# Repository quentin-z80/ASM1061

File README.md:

# ASM1061

ASM1061 based PCIe to SATA card

Manufactured using JLCPCB's JLC3313 stackup

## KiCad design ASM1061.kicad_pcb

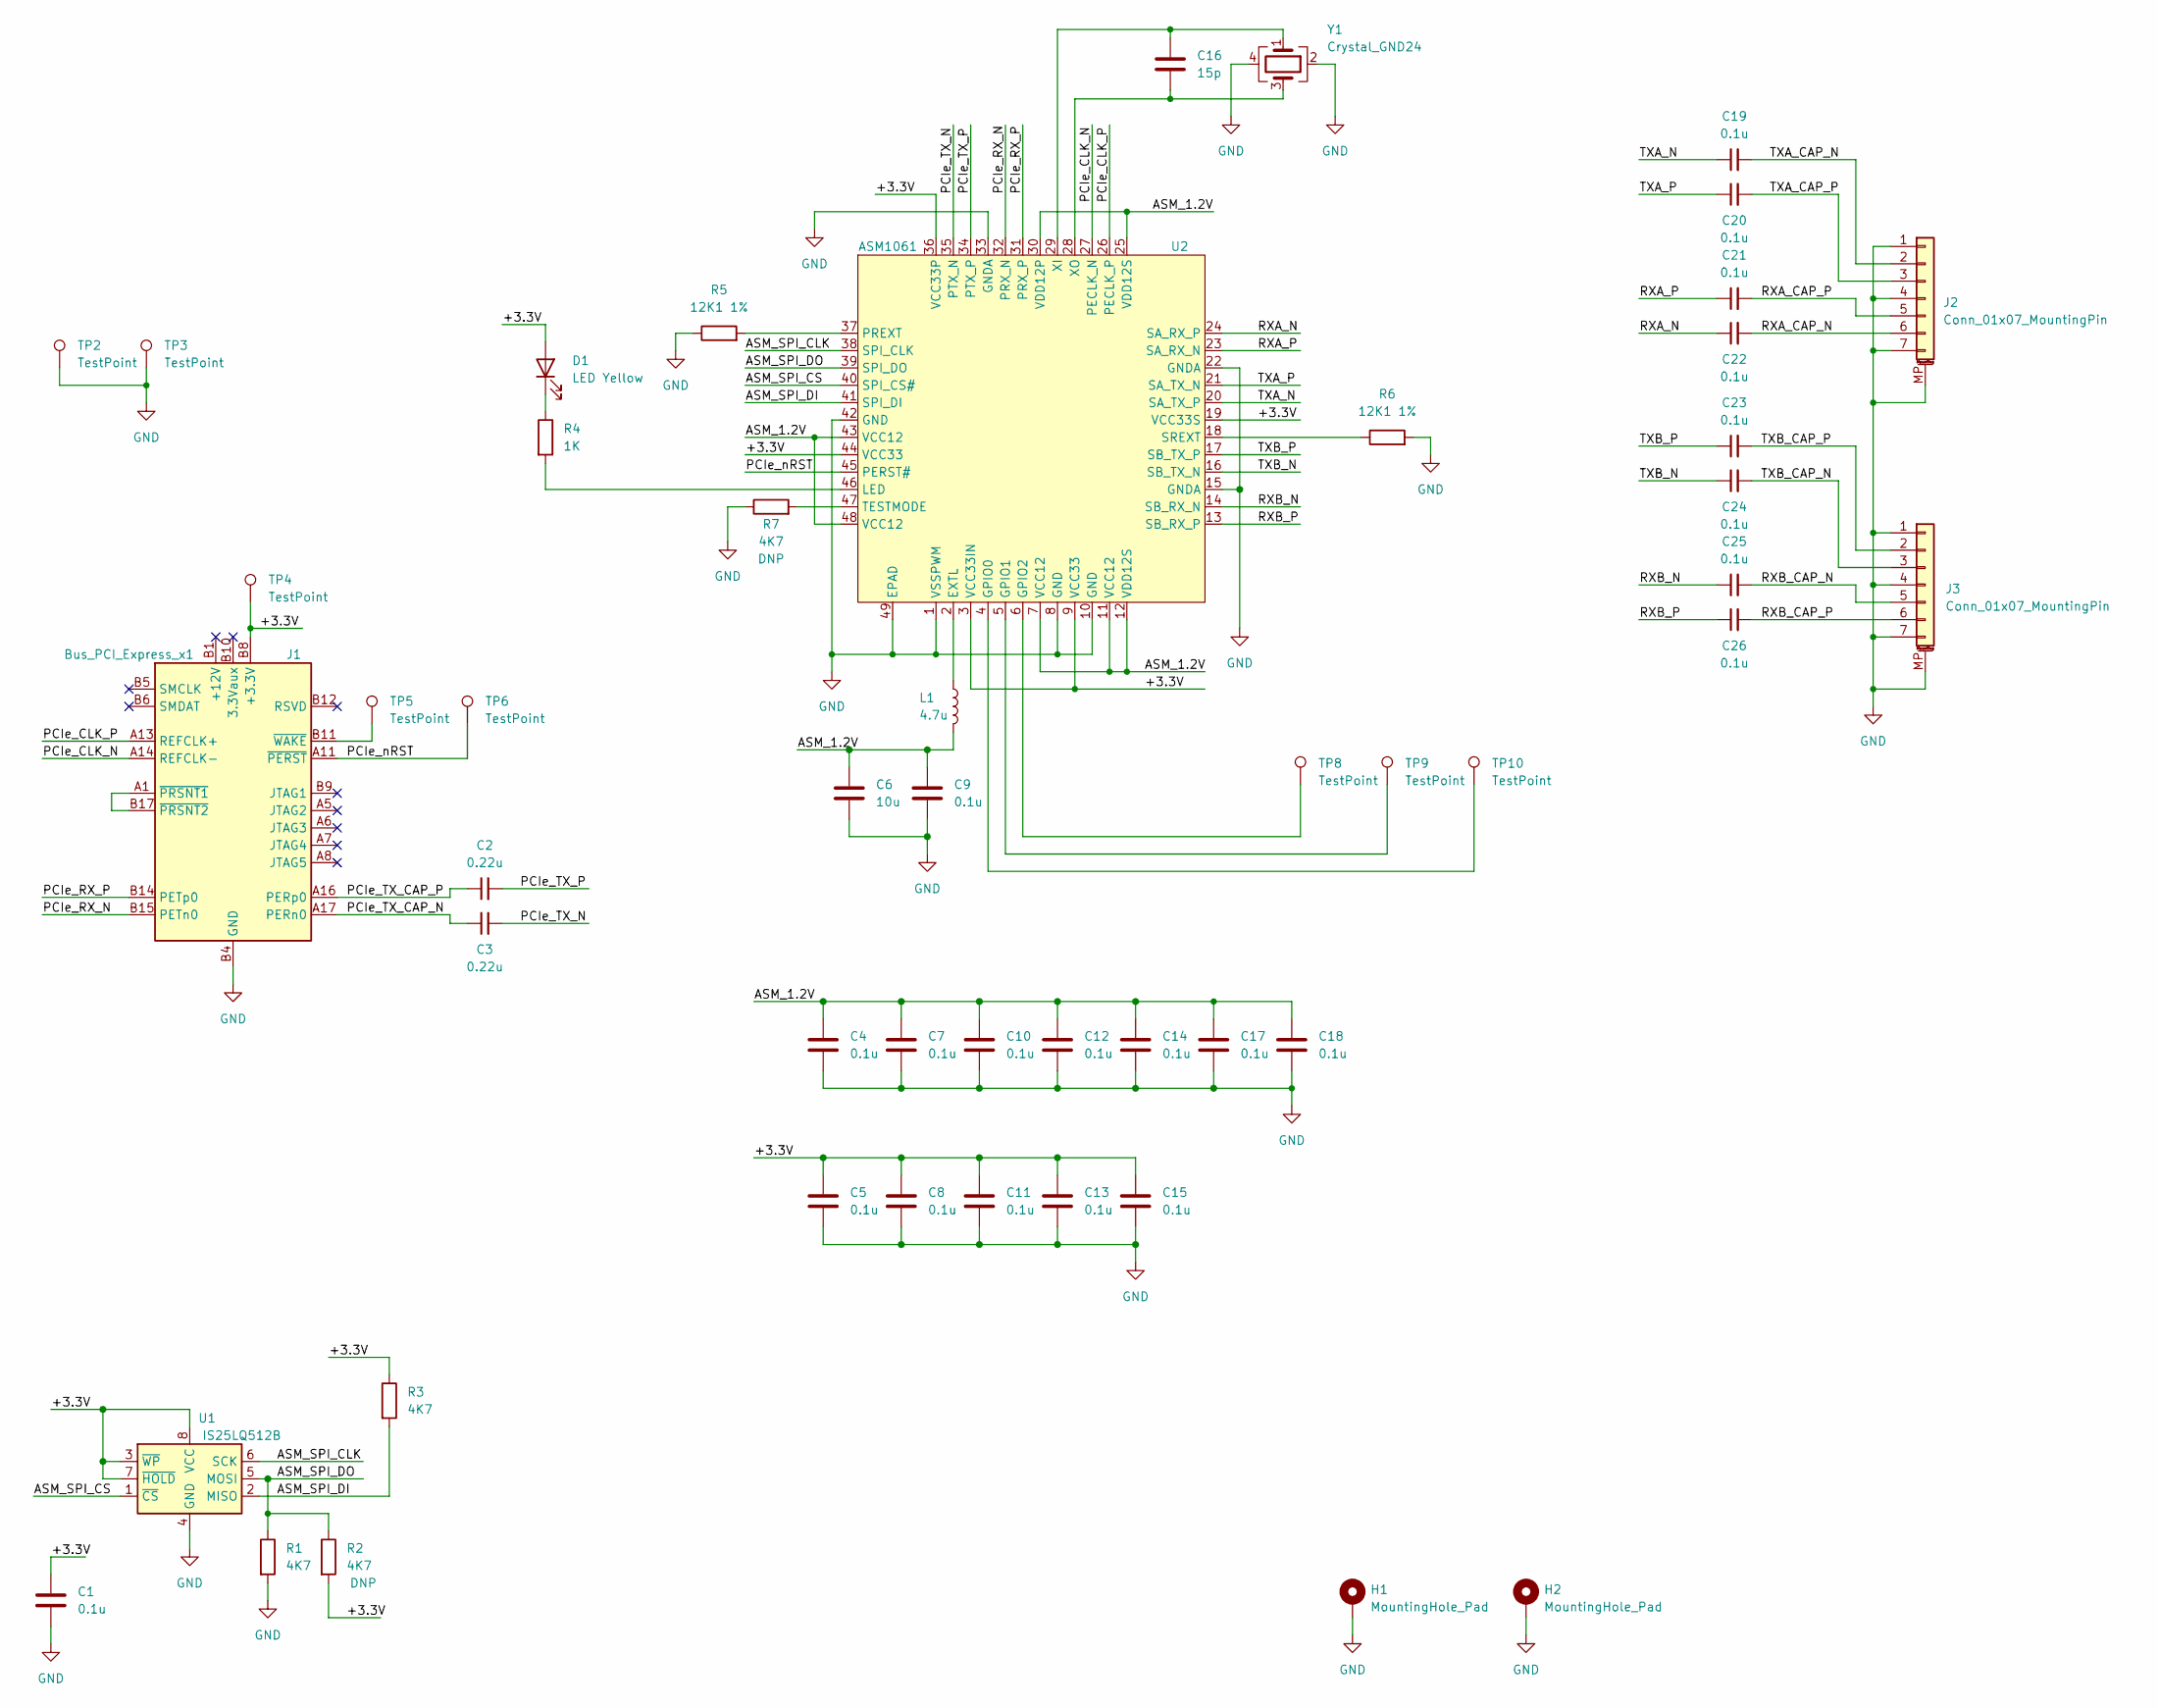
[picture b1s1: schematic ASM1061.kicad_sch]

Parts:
C1, C4, C5, C7, C8, C9, C10, C11, C12, C13, C14, C15, C17, C18, C19, C20, C21, C22, C23, C24, C25, C26: 0.1u; C_0402_1005Metric; MFG_PN GCM155R71C104KA55D; DigiKey_PN 490-4759-1-ND
C2, C3: 0.22u; C_0402_1005Metric; MFG_PN GCM155R71C224KE02D; DigiKey_PN 490-10671-1-ND
C6: 10u; C_0805_2012Metric; MFG_PN GRM21BR70J106KA73L; DigiKey_PN 490-GRM21BR70J106KA73LCT-ND
C16: 15p; C_0402_1005Metric; MFG_PN GCM1555C1H150JA16D; DigiKey_PN 490-11147-1-ND
D1: LED Yellow; LED_0603_1608Metric; MFG_PN SML-D12Y1WT86; DigiKey_PN SML-D12Y1WT86CT-ND
H1, H2: MountingHole_Pad; MountingHole_3.2mm_M3_Pad_Via
J1: Bus_PCI_Express_x1; BUS_PCIexpress_x1
J2, J3: Conn_01x07_MountingPin; 0674901220; MFG_PN 0470804005; DigiKey_PN WM19112CT-ND
L1: 4.7u; L_1008_2520Metric; MFG_PN CVH252009-4R7M; DigiKey_PN CVH252009-4R7MCT-ND
R1, R2, R3, R7: 4K7; R_0402_1005Metric; MFG_PN RC0402JR-074K7L; DigiKey_PN 311-4.7KJRCT-ND
R4: 1K; R_0402_1005Metric; MFG_PN RC0402JR-071KL; DigiKey_PN 311-1.0KJRCT-ND
R5, R6: 12K1 1%; R_0402_1005Metric; MFG_PN RC0402FR-0712K1L; DigiKey_PN 311-12.1KLRCT-ND
TP2, TP3, TP4, TP5, TP6, TP8, TP9, TP10: TestPoint; TestPoint_Pad_D1.5mm
U1: IS25LQ512B; SOIC-8_3.9x4.9mm_P1.27mm; MFG_PN IS25LQ512B-JNLE; DigiKey_PN 706-1325-ND
U2: ASM1061; VQFN-48-1EP_7x7mm_P0.5mm_EP4.1x4.1mm_ThermalVias
Y1: Crystal_GND24; Crystal_SMD_3225-4Pin_3.2x2.5mm; MFG_PN CX3225SB20000H0FLJCC; DigiKey_PN 1253-1744-1-ND

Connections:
/+3.3V: C1.1, C5.1, C8.1, C11.1, C13.1, C15.1, D1.2 (A), J1.A9 (+3.3V), J1.A10 (+3.3V), J1.B8 (+3.3V), R2.2, R3.1, TP4.1, U1.3 (~WP), U1.7 (~HOLD), U1.8 (VCC), U2.3 (VCC33IN), U2.9 (VCC33), U2.19 (VCC33S), U2.36 (VCC33P), U2.44 (VCC33)
/ASM_1.2V: C4.1, C6.1, C7.1, C9.1, C10.1, C12.1, C14.1, C17.1, C18.1, L1.2, U2.7 (VCC12), U2.11 (VCC12), U2.12 (VDD12S), U2.25 (VDD12S), U2.30 (VDD12P), U2.43 (VCC12), U2.48 (VCC12)
/ASM_SPI_CLK: U1.6 (SCK), U2.38 (SPI_CLK)
/ASM_SPI_CS: U1.1 (~CS), U2.40 (SPI_CS#)
/ASM_SPI_DI: R3.2, U1.2 (MISO), U2.41 (SPI_DI)
/ASM_SPI_DO: R1.1, R2.1, U1.5 (MOSI), U2.39 (SPI_DO)
/PCIe_CLK_N: J1.A14 (REFCLK-), U2.27 (PECLK_N)
/PCIe_CLK_P: J1.A13 (REFCLK+), U2.26 (PECLK_P)
/PCIe_RX_N: J1.B15 (PETn0), U2.32 (PRX_N)
/PCIe_RX_P: J1.B14 (PETp0), U2.31 (PRX_P)
/PCIe_TX_CAP_N: C3.1, J1.A17 (PERn0)
/PCIe_TX_CAP_P: C2.1, J1.A16 (PERp0)
/PCIe_TX_N: C3.2, U2.35 (PTX_N)
/PCIe_TX_P: C2.2, U2.34 (PTX_P)
/PCIe_nRST: J1.A11 (~PERST), TP6.1, U2.45 (PERST#)
/RXA_CAP_N: C22.2, J2.6
/RXA_CAP_P: C21.2, J2.5
/RXA_N: C22.1, U2.24 (SA_RX_P)
/RXA_P: C21.1, U2.23 (SA_RX_N)
/RXB_CAP_N: C25.2, J3.5
/RXB_CAP_P: C26.2, J3.6
/RXB_N: C25.1, U2.14 (SB_RX_N)
/RXB_P: C26.1, U2.13 (SB_RX_P)
/TXA_CAP_N: C19.2, J2.2
/TXA_CAP_P: C20.2, J2.3
/TXA_N: C19.1, U2.20 (SA_TX_P)
/TXA_P: C20.1, U2.21 (SA_TX_N)
/TXB_CAP_N: C24.2, J3.3
/TXB_CAP_P: C23.2, J3.2
/TXB_N: C24.1, U2.16 (SB_TX_N)
/TXB_P: C23.1, U2.17 (SB_TX_P)
GND: C1.2, C4.2, C5.2, C6.2, C7.2, C8.2, C9.2, C10.2, C11.2, C12.2, C13.2, C14.2, C15.2, C17.2, C18.2, H1.1, H2.1, J1.A4 (GND), J1.A12 (GND), J1.A15 (GND), J1.A18 (GND), J1.B4 (GND), J1.B7 (GND), J1.B13 (GND), J1.B16 (GND), J1.B18 (GND), J2.1, J2.4, J2.7, J2.MP (MountPin), J3.1, J3.4, J3.7, J3.MP (MountPin), R1.2, R5.1, R6.2, R7.1, TP2.1, TP3.1, U1.4 (GND), U2.1 (VSSPWM), U2.8 (GND), U2.10 (GND), U2.15 (GNDA), U2.22 (GNDA), U2.33 (GNDA), U2.42 (GND), U2.49 (EPAD), Y1.2, Y1.4
unnamed: C16.1, U2.29 (XI), Y1.1
unnamed: C16.2, U2.28 (XO), Y1.3
unnamed: D1.1 (K), R4.1
unnamed: J1.A1 (~PRSNT1), J1.B17 (~PRSNT2)
unnamed: J1.B11 (~WAKE), TP5.1
unnamed: L1.1, U2.2 (EXTL)
unnamed: R4.2, U2.46 (LED)
unnamed: R5.2, U2.37 (PREXT)
unnamed: R6.1, U2.18 (SREXT)
unnamed: R7.2, U2.47 (TESTMODE)
unnamed: TP8.1, U2.6 (GPIO2)
unnamed: TP9.1, U2.5 (GPIO1)
unnamed: TP10.1, U2.4 (GPIO0)

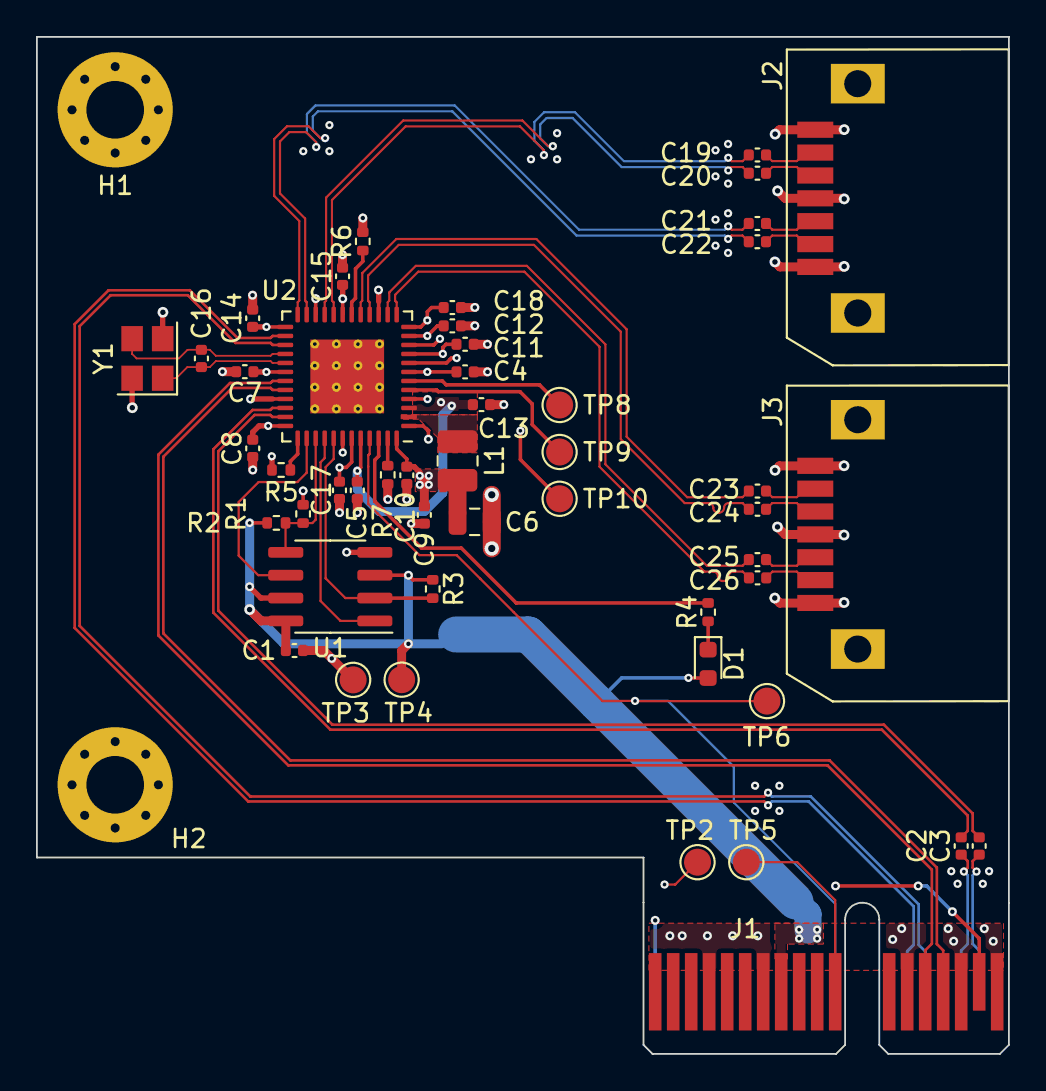
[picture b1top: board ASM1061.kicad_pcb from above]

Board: 4 copper layers, 54.0 x 56.5 mm, 51 parts (0 on the bottom side), 45 nets.

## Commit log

2022-03-01 import project into git
2022-03-01 add README
2022-03-02 Add LICENSE
2022-04-28 rename LICENSE to UNLICENSE
2022-04-28 README: swap real pic and render
2022-08-09 resave files in new kicad version
2022-08-09 README.md: add pcb manufacturing info
2022-08-09 use solid ground pour for asm1061, increase power trace size
2024-04-08 give credit for ahci / ide id bits, upload 4.27 rom
